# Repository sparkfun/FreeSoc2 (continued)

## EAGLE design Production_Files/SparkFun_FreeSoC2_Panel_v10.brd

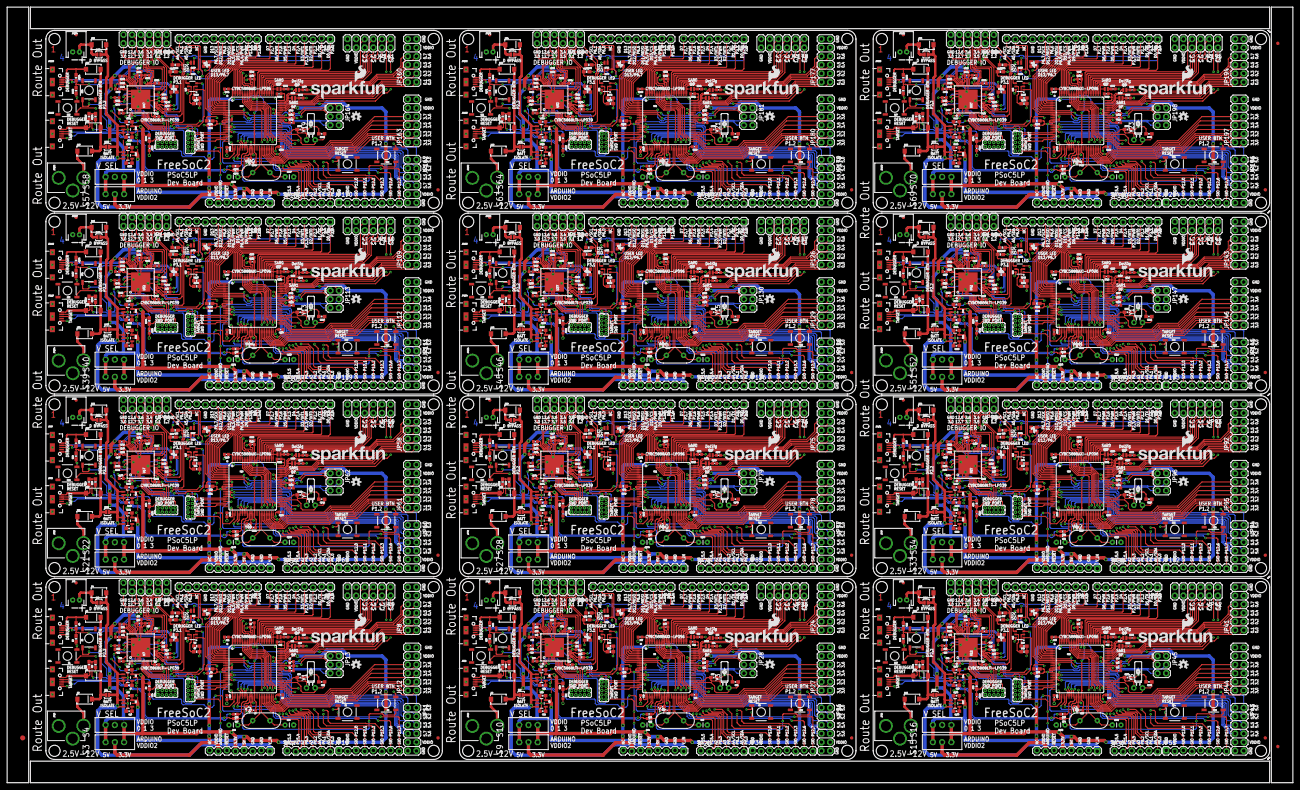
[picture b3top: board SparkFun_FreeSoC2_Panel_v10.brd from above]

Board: 4 copper layers, 379.0 x 228.6 mm, 1263 parts (0 on the bottom side), 1512 nets.

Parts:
C1, C2, C4, C5, C7, C16, C17, C19, C20, C39, C40, C41, C44, C45, C50, C51, C52, C53, C77, C78, C79, C82, C83, C88, C89, C90, C91, C115, C116, C117, C120, C121, C126, C127, C128, C129, C153, C154, C155, C158, C159, C164, C165, C166, C167, C191, C192, C193, C196, C197, C202, C203, C204, C205, C229, C230, C231, C234, C235, C240, C241, C242, C243, C267, C268, C269, C272, C273, C278, C279, C280, C281, C305, C306, C307, C310, C311, C316, C317, C318, C319, C343, C344, C345, C348, C349, C354, C355, C356, C357, C381, C382, C383, C386, C387, C392, C393, C394, C395, C419, C420, C421, C424, C425, C430, C431, C432, C433: 1.0uF; 0402-CAP
C3, C6, C9, C11, C13, C15, C21, C22, C23, C25, C27, C29, C30, C31, C32, C33, C34, C35, C36, C37, C38, C42, C43, C46, C47, C48, C49, C54, C55, C56, C57, C58, C59, C60, C69, C70, C71, C72, C73, C74, C75, C76, C80, C81, C84, C85, C86, C87, C92, C93, C94, C95, C96, C97, C98, C107, C108, C109, C110, C111, C112, C113, C114, C118, C119, C122, C123, C124, C125, C130, C131, C132, C133, C134, C135, C136, C145, C146, C147, C148, C149, C150, C151, C152, C156, C157, C160, C161, C162, C163, C168, C169, C170, C171, C172, C173, C174, C183, C184, C185, C186, C187, C188, C189, C190, C194, C195, C198, C199, C200, C201, C206, C207, C208, C209, C210, C211, C212, C221, C222, C223, C224, C225, C226, C227, C228, C232, C233, C236, C237, C238, C239, C244, C245, C246, C247, C248, C249, C250, C259, C260, C261, C262, C263, C264, C265, C266, C270, C271, C274, C275, C276, C277, C282, C283, C284, C285, C286, C287, C288, C297, C298, C299, C300, C301, C302, C303, C304, C308, C309, C312, C313, C314, C315, C320, C321, C322, C323, C324, C325, C326, C335, C336, C337, C338, C339, C340, C341, C342, C346, C347, C350, C351, C352, C353, C358, C359, C360, C361, C362, C363, C364, C373, C374, C375, C376, C377, C378, C379, C380, C384, C385, C388, C389, C390, C391, C396, C397, C398, C399, C400, C401, C402, C411, C412, C413, C414, C415, C416, C417, C418, C422, C423, C426, C427, C428, C429, C434, C435, C436, C437, C438, C439, C440, C449, C450, C451, C452, C453, C454, C455, C456: 0.1uF; 0402-CAP
C8, C10, C61, C62, C99, C100, C137, C138, C175, C176, C213, C214, C251, C252, C289, C290, C327, C328, C365, C366, C403, C404, C441, C442: 470pF; 0603-CAP
C12, C14, C63, C64, C101, C102, C139, C140, C177, C178, C215, C216, C253, C254, C291, C292, C329, C330, C367, C368, C405, C406, C443, C444: CAP-PTH-SMALL
C18, C24, C65, C66, C103, C104, C141, C142, C179, C180, C217, C218, C255, C256, C293, C294, C331, C332, C369, C370, C407, C408, C445, C446: 22pF; 0603-CAP
C26, C28, C67, C68, C105, C106, C143, C144, C181, C182, C219, C220, C257, C258, C295, C296, C333, C334, C371, C372, C409, C410, C447, C448: 2.2uF; 0603-CAP
D1, D2, D3, D4, D7, D8, D9, D10, D13, D14, D15, D16, D19, D20, D21, D22, D25, D26, D27, D28, D31, D32, D33, D34, D37, D38, D39, D40, D43, D44, D45, D46, D49, D50, D51, D52, D55, D56, D57, D58, D61, D62, D63, D64, D67, D68, D69, D70: MBRA140; SMA-DIODE
D5, D6, D11, D12, D17, D18, D23, D24, D29, D30, D35, D36, D41, D42, D47, D48, D53, D54, D59, D60, D65, D66, D71, D72: RED; LED-0603
E$1: FIDUCIAL-1.5X3
E$4, E$5: FIDUCIAL-1X2
FID1, FID2, FID3, FID4, FID5, FID6, FID7, FID8, FID9, FID10, FID11, FID12, FID13, FID14, FID15, FID16, FID17, FID18, FID19, FID20, FID21, FID22, FID23, FID24: FIDUCIAL1X2; FIDUCIAL-1X2
JP1, JP2, JP32, JP33, JP49, JP50, JP66, JP67, JP83, JP84, JP100, JP101, JP117, JP118, JP134, JP135, JP151, JP152, JP168, JP169, JP185, JP186, JP202, JP203: MicroB; USB-B-MICRO-SMD_V03
JP3, JP16, JP35, JP52, JP69, JP86, JP103, JP120, JP137, JP154, JP171, JP188: M02JST-PTH-2; JST-2-PTH
JP4, JP20, JP37, JP54, JP71, JP88, JP105, JP122, JP139, JP156, JP173, JP190: 1X6 FEMALE PTH; 1X06-SIP_LOCK
JP5, JP6, JP21, JP22, JP38, JP39, JP55, JP56, JP72, JP73, JP89, JP90, JP106, JP107, JP123, JP124, JP140, JP141, JP157, JP158, JP174, JP175, JP191, JP192: 1X8 FEMALE PTH; 1X08_LOCK
JP7, JP23, JP40, JP57, JP74, JP91, JP108, JP125, JP142, JP159, JP176, JP193: 1X10 FEMALE PTH; 1X10_LOCK
JP8, JP9, JP11, JP12, JP15, JP24, JP25, JP26, JP27, JP30, JP41, JP42, JP43, JP44, JP47, JP58, JP59, JP60, JP61, JP64, JP75, JP76, JP77, JP78, JP81, JP92, JP93, JP94, JP95, JP98, JP109, JP110, JP111, JP112, JP115, JP126, JP127, JP128, JP129, JP132, JP143, JP144, JP145, JP146, JP149, JP160, JP161, JP162, JP163, JP166, JP177, JP178, JP179, JP180, JP183, JP194, JP195, JP196, JP197, JP200: 2X6 FEMALE; 2X6
JP10, JP34, JP51, JP68, JP85, JP102, JP119, JP136, JP153, JP170, JP187, JP204: 1x8 FEMALE PTH; 1X08_LOCK
JP13, JP28, JP45, JP62, JP79, JP96, JP113, JP130, JP147, JP164, JP181, JP198: 2X3
JP14, JP17, JP29, JP31, JP46, JP48, JP63, JP65, JP80, JP82, JP97, JP99, JP114, JP116, JP131, JP133, JP148, JP150, JP165, JP167, JP182, JP184, JP199, JP201: DNP; 2X5_PTH_SILK_.05
JP18, JP19, JP36, JP53, JP70, JP87, JP104, JP121, JP138, JP155, JP172, JP189: POWER_JACKPTH_LOCK; POWER_JACK_PTH_LOCK
LOGO1, LOGO3, LOGO5, LOGO7, LOGO9, LOGO11, LOGO13, LOGO15, LOGO17, LOGO19, LOGO21, LOGO23: SFE_LOGO_NAME_FLAME.2_INCH; SFE_LOGO_NAME_FLAME_.2
LOGO2, LOGO4, LOGO6, LOGO8, LOGO10, LOGO12, LOGO14, LOGO16, LOGO18, LOGO20, LOGO22, LOGO24: OSHW-LOGOS; OSHW-LOGO-S
R1, R2, R23, R24, R39, R40, R55, R56, R71, R72, R87, R88, R103, R104, R119, R120, R135, R136, R151, R152, R167, R168, R183, R184: 4.7K; 0603-RES
R3, R4, R25, R26, R41, R42, R57, R58, R73, R74, R89, R90, R105, R106, R121, R122, R137, R138, R153, R154, R169, R170, R185, R186: 10K; 0603-RES
R5, R6, R27, R28, R43, R44, R59, R60, R75, R76, R91, R92, R107, R108, R123, R124, R139, R140, R155, R156, R171, R172, R187, R188: 20k; 0603-RES
R7, R8, R29, R30, R45, R46, R61, R62, R77, R78, R93, R94, R109, R110, R125, R126, R141, R142, R157, R158, R173, R174, R189, R190: 2.2k; 0603-RES
R9, R10, R15, R20, R21, R22, R31, R32, R37, R38, R47, R48, R53, R54, R63, R64, R69, R70, R79, R80, R85, R86, R95, R96, R101, R102, R111, R112, R117, R118, R127, R128, R133, R134, R143, R144, R149, R150, R159, R160, R165, R166, R175, R176, R181, R182, R191, R192: 1K; 0603-RES
R11, R12, R13, R14, R16, R17, R18, R19, R33, R34, R35, R36, R49, R50, R51, R52, R65, R66, R67, R68, R81, R82, R83, R84, R97, R98, R99, R100, R113, R114, R115, R116, R129, R130, R131, R132, R145, R146, R147, R148, R161, R162, R163, R164, R177, R178, R179, R180: 22; 0402-RES
S1, S2, S5, S6, S7, S8, S11, S12, S13, S14, S17, S18, S19, S20, S23, S24, S25, S26, S29, S30, S31, S32, S35, S36, S37, S38, S41, S42, S43, S44, S47, S48, S49, S50, S53, S54, S55, S56, S59, S60, S61, S62, S65, S66, S67, S68, S71, S72: SPST-MOM; TACTILE-SWITCH-SMD
S3, S4, S9, S10, S15, S16, S21, S22, S27, S28, S33, S34, S39, S40, S45, S46, S51, S52, S57, S58, S63, S64, S69, S70: SPDT; SWITCH-SPDT_LOCK.007S
SJ1, SJ8, SJ15, SJ22, SJ29, SJ36, SJ43, SJ50, SJ57, SJ64, SJ71, SJ78: JUMPER-PAD-2-NC_BY_PASTE; PAD-JUMPER-2-NC_BY_PASTE_YES_SILK
SJ2, SJ9, SJ16, SJ23, SJ30, SJ37, SJ44, SJ51, SJ58, SJ65, SJ72, SJ79: JUMPER-PAD-2-NOYES_SILK; PAD-JUMPER-2-NO_YES_SILK
SJ3, SJ4, SJ5, SJ6, SJ7, SJ10, SJ11, SJ12, SJ13, SJ14, SJ17, SJ18, SJ19, SJ20, SJ21, SJ24, SJ25, SJ26, SJ27, SJ28, SJ31, SJ32, SJ33, SJ34, SJ35, SJ38, SJ39, SJ40, SJ41, SJ42, SJ45, SJ46, SJ47, SJ48, SJ49, SJ52, SJ53, SJ54, SJ55, SJ56, SJ59, SJ60, SJ61, SJ62, SJ63, SJ66, SJ67, SJ68, SJ69, SJ70, SJ73, SJ74, SJ75, SJ76, SJ77, SJ80, SJ81, SJ82, SJ83, SJ84: JUMPER-PAD-2-NO; PAD-JUMPER-2-NO_NO_SILK
STANDOFF1, STANDOFF2, STANDOFF3, STANDOFF4, STANDOFF5, STANDOFF6, STANDOFF7, STANDOFF8, STANDOFF9, STANDOFF10, STANDOFF11, STANDOFF12, STANDOFF13, STANDOFF14, STANDOFF15, STANDOFF16, STANDOFF17, STANDOFF18, STANDOFF19, STANDOFF20, STANDOFF21, STANDOFF22, STANDOFF23, STANDOFF24, STANDOFF25, STANDOFF26, STANDOFF27, STANDOFF28, STANDOFF29, STANDOFF30, STANDOFF31, STANDOFF32, STANDOFF33, STANDOFF34, STANDOFF35, STANDOFF36, STANDOFF37, STANDOFF38, STANDOFF39, STANDOFF40, STANDOFF41, STANDOFF42, STANDOFF43, STANDOFF44, STANDOFF45, STANDOFF46, STANDOFF47, STANDOFF48: STAND-OFF
U1, U5, U11, U16, U21, U26, U31, U36, U41, U46, U51, U56: CY8C5888AXI-LP096; TQFP-100-14X14MM
U2, U8, U13, U18, U23, U28, U33, U38, U43, U48, U53, U58: MIC5219 5V; SOT23-5
U3, U9, U14, U19, U24, U29, U34, U39, U44, U49, U54, U59: MIC5219 3.3V; SOT23-5
U4, U10, U15, U20, U25, U30, U35, U40, U45, U50, U55, U60: 2A/20V; SOT26
U6, U7, U12, U17, U22, U27, U32, U37, U42, U47, U52, U57: CY8C5868LTI-LP039; QFN-68
Y1, Y3, Y5, Y7, Y9, Y11, Y13, Y15, Y17, Y19, Y21, Y23: 32.768kHz; TC26H
Y2, Y4, Y6, Y8, Y10, Y12, Y14, Y16, Y18, Y20, Y22, Y24: HC49US

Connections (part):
3.3V: C2.1, C3.1, C4.1, C19.1, C21.1, C22.1, C26.2, JP6.5, R1.2, R2.2, S3.3, S4.3, U1.37, U1.88, U3.5, U7.24, U7.59
3.3V1: C40.1, C43.1, C44.1, C52.1, C54.1, C55.1, C67.2, JP22.5, R23.2, R24.2, S9.3, S10.3, U5.37, U5.88, U6.24, U6.59, U9.5
3.3V2: C78.1, C81.1, C82.1, C90.1, C92.1, C93.1, C105.2, JP39.5, R39.2, R40.2, S15.3, S16.3, U11.37, U11.88, U12.24, U12.59, U14.5
3.3V3: C116.1, C119.1, C120.1, C128.1, C130.1, C131.1, C143.2, JP56.5, R55.2, R56.2, S21.3, S22.3, U16.37, U16.88, U17.24, U17.59, U19.5
3.3V4: C154.1, C157.1, C158.1, C166.1, C168.1, C169.1, C181.2, JP73.5, R71.2, R72.2, S27.3, S28.3, U21.37, U21.88, U22.24, U22.59, U24.5
3.3V5: C192.1, C195.1, C196.1, C204.1, C206.1, C207.1, C219.2, JP90.5, R87.2, R88.2, S33.3, S34.3, U26.37, U26.88, U27.24, U27.59, U29.5
3.3V6: C230.1, C233.1, C234.1, C242.1, C244.1, C245.1, C257.2, JP107.5, R103.2, R104.2, S39.3, S40.3, U31.37, U31.88, U32.24, U32.59, U34.5
3.3V7: C268.1, C271.1, C272.1, C280.1, C282.1, C283.1, C295.2, JP124.5, R119.2, R120.2, S45.3, S46.3, U36.37, U36.88, U37.24, U37.59, U39.5
3.3V8: C306.1, C309.1, C310.1, C318.1, C320.1, C321.1, C333.2, JP141.5, R135.2, R136.2, S51.3, S52.3, U41.37, U41.88, U42.24, U42.59, U44.5
3.3V9: C344.1, C347.1, C348.1, C356.1, C358.1, C359.1, C371.2, JP158.5, R151.2, R152.2, S57.3, S58.3, U46.37, U46.88, U47.24, U47.59, U49.5
3.3V10: C382.1, C385.1, C386.1, C394.1, C396.1, C397.1, C409.2, JP175.5, R167.2, R168.2, S63.3, S64.3, U51.37, U51.88, U52.24, U52.59, U54.5
3.3V11: C420.1, C423.1, C424.1, C432.1, C434.1, C435.1, C447.2, JP192.5, R183.2, R184.2, S69.3, S70.3, U56.37, U56.88, U57.24, U57.59, U59.5
5V: C5.1, C6.1, C20.1, C23.1, C28.2, JP6.4, S3.1, S4.1, U1.65, U2.5, U7.44
5V1: C41.1, C42.1, C53.1, C56.1, C68.2, JP22.4, S9.1, S10.1, U5.65, U6.44, U8.5
5V2: C79.1, C80.1, C91.1, C94.1, C106.2, JP39.4, S15.1, S16.1, U11.65, U12.44, U13.5
5V3: C117.1, C118.1, C129.1, C132.1, C144.2, JP56.4, S21.1, S22.1, U16.65, U17.44, U18.5
5V4: C155.1, C156.1, C167.1, C170.1, C182.2, JP73.4, S27.1, S28.1, U21.65, U22.44, U23.5
5V5: C193.1, C194.1, C205.1, C208.1, C220.2, JP90.4, S33.1, S34.1, U26.65, U27.44, U28.5
5V6: C231.1, C232.1, C243.1, C246.1, C258.2, JP107.4, S39.1, S40.1, U31.65, U32.44, U33.5
5V7: C269.1, C270.1, C281.1, C284.1, C296.2, JP124.4, S45.1, S46.1, U36.65, U37.44, U38.5
5V8: C307.1, C308.1, C319.1, C322.1, C334.2, JP141.4, S51.1, S52.1, U41.65, U42.44, U43.5
5V9: C345.1, C346.1, C357.1, C360.1, C372.2, JP158.4, S57.1, S58.1, U46.65, U47.44, U48.5
5V10: C383.1, C384.1, C395.1, C398.1, C410.2, JP175.4, S63.1, S64.1, U51.65, U52.44, U53.5
5V11: C421.1, C422.1, C433.1, C436.1, C448.2, JP192.4, S69.1, S70.1, U56.65, U57.44, U58.5
!DEBUG_P2.6_SCL_PU_EN: U4.G2, U7.1
!DEBUG_P2.6_SCL_PU_EN1: U6.1, U10.G2
!DEBUG_P2.6_SCL_PU_EN2: U12.1, U15.G2
!DEBUG_P2.6_SCL_PU_EN3: U17.1, U20.G2
!DEBUG_P2.6_SCL_PU_EN4: U22.1, U25.G2
!DEBUG_P2.6_SCL_PU_EN5: U27.1, U30.G2
!DEBUG_P2.6_SCL_PU_EN6: U32.1, U35.G2
!DEBUG_P2.6_SCL_PU_EN7: U37.1, U40.G2
!DEBUG_P2.6_SCL_PU_EN8: U42.1, U45.G2
!DEBUG_P2.6_SCL_PU_EN9: U47.1, U50.G2
!DEBUG_P2.6_SCL_PU_EN10: U52.1, U55.G2
!DEBUG_P2.6_SCL_PU_EN11: U57.1, U60.G2
!DEBUG_P2.7_SDA_PU_EN: U4.G1, U7.2
!DEBUG_P2.7_SDA_PU_EN1: U6.2, U10.G1
!DEBUG_P2.7_SDA_PU_EN2: U12.2, U15.G1
!DEBUG_P2.7_SDA_PU_EN3: U17.2, U20.G1
!DEBUG_P2.7_SDA_PU_EN4: U22.2, U25.G1
!DEBUG_P2.7_SDA_PU_EN5: U27.2, U30.G1
!DEBUG_P2.7_SDA_PU_EN6: U32.2, U35.G1
!DEBUG_P2.7_SDA_PU_EN7: U37.2, U40.G1
!DEBUG_P2.7_SDA_PU_EN8: U42.2, U45.G1
!DEBUG_P2.7_SDA_PU_EN9: U47.2, U50.G1
!DEBUG_P2.7_SDA_PU_EN10: U52.2, U55.G1
!DEBUG_P2.7_SDA_PU_EN11: U57.2, U60.G1
!DEBUG_RESET: C38.1, JP14.10, R2.1, S1.1, U7.10
!DEBUG_RESET1: C76.1, JP29.10, R24.1, S7.1, U6.10
!DEBUG_RESET2: C114.1, JP46.10, R40.1, S13.1, U12.10
!DEBUG_RESET3: C152.1, JP63.10, R56.1, S19.1, U17.10
!DEBUG_RESET4: C190.1, JP80.10, R72.1, S25.1, U22.10
!DEBUG_RESET5: C228.1, JP97.10, R88.1, S31.1, U27.10
!DEBUG_RESET6: C266.1, JP114.10, R104.1, S37.1, U32.10
!DEBUG_RESET7: C304.1, JP131.10, R120.1, S43.1, U37.10
!DEBUG_RESET8: C342.1, JP148.10, R136.1, S49.1, U42.10
!DEBUG_RESET9: C380.1, JP165.10, R152.1, S55.1, U47.10
!DEBUG_RESET10: C418.1, JP182.10, R168.1, S61.1, U52.10
!DEBUG_RESET11: C456.1, JP199.10, R184.1, S67.1, U57.10
!RESET: C37.1, JP6.6, JP13.5, JP17.10, R1.1, S2.1, U1.15, U7.3
!RESET1: C75.1, JP22.6, JP28.5, JP31.10, R23.1, S8.1, U5.15, U6.3
!RESET2: C113.1, JP39.6, JP45.5, JP48.10, R39.1, S14.1, U11.15, U12.3
!RESET3: C151.1, JP56.6, JP62.5, JP65.10, R55.1, S20.1, U16.15, U17.3
!RESET4: C189.1, JP73.6, JP79.5, JP82.10, R71.1, S26.1, U21.15, U22.3
!RESET5: C227.1, JP90.6, JP96.5, JP99.10, R87.1, S32.1, U26.15, U27.3
!RESET6: C265.1, JP107.6, JP113.5, JP116.10, R103.1, S38.1, U31.15, U32.3
!RESET7: C303.1, JP124.6, JP130.5, JP133.10, R119.1, S44.1, U36.15, U37.3
!RESET8: C341.1, JP141.6, JP147.5, JP150.10, R135.1, S50.1, U41.15, U42.3
!RESET9: C379.1, JP158.6, JP164.5, JP167.10, R151.1, S56.1, U46.15, U47.3
!RESET10: C417.1, JP175.6, JP181.5, JP184.10, R167.1, S62.1, U51.15, U52.3
!RESET11: C455.1, JP192.6, JP198.5, JP201.10, R183.1, S68.1, U56.15, U57.3
A0: JP4.1, U1.94
A1: JP4.2, U1.93
A2: JP4.3, U1.92
A3: JP4.4, U1.91
A4: JP4.5, JP7.10, SJ7.1, U1.90
A5: JP4.6, JP7.9, SJ6.1, U1.89
A6: JP20.1, U5.94
A7: JP20.2, U5.93
A8: JP20.6, JP23.9, SJ13.1, U5.89
A9: JP20.5, JP23.10, SJ14.1, U5.90
A10: JP20.3, U5.92
A11: JP20.4, U5.91
A12: JP37.1, U11.94
A13: JP37.2, U11.93
A14: JP37.6, JP40.9, SJ20.1, U11.89
A15: JP37.5, JP40.10, SJ21.1, U11.90
A16: JP37.3, U11.92
A17: JP37.4, U11.91
A18: JP54.1, U16.94
A19: JP54.2, U16.93
A20: JP54.6, JP57.9, SJ27.1, U16.89
A21: JP54.5, JP57.10, SJ28.1, U16.90
A22: JP54.3, U16.92
A23: JP54.4, U16.91
A24: JP71.1, U21.94
A25: JP71.2, U21.93
A26: JP71.6, JP74.9, SJ34.1, U21.89
A27: JP71.5, JP74.10, SJ35.1, U21.90
A28: JP71.3, U21.92
A29: JP71.4, U21.91
A30: JP88.1, U26.94
A31: JP88.2, U26.93
A32: JP88.6, JP91.9, SJ41.1, U26.89
A33: JP88.5, JP91.10, SJ42.1, U26.90
A34: JP88.3, U26.92
A35: JP88.4, U26.91
A36: JP105.1, U31.94
A37: JP105.2, U31.93
A38: JP105.6, JP108.9, SJ48.1, U31.89
A39: JP105.5, JP108.10, SJ49.1, U31.90
A40: JP105.3, U31.92
A41: JP105.4, U31.91
A42: JP122.1, U36.94
A43: JP122.2, U36.93
A44: JP122.6, JP125.9, SJ55.1, U36.89
A45: JP122.5, JP125.10, SJ56.1, U36.90
A46: JP122.3, U36.92
A47: JP122.4, U36.91
A48: JP139.1, U41.94
A49: JP139.2, U41.93
A50: JP139.6, JP142.9, SJ62.1, U41.89
A51: JP139.5, JP142.10, SJ63.1, U41.90
A52: JP139.3, U41.92
A53: JP139.4, U41.91
A54: JP156.1, U46.94
A55: JP156.2, U46.93
A56: JP156.6, JP159.9, SJ69.1, U46.89
A57: JP156.5, JP159.10, SJ70.1, U46.90
A58: JP156.3, U46.92
A59: JP156.4, U46.91
A60: JP173.1, U51.94
A61: JP173.2, U51.93
A62: JP173.6, JP176.9, SJ76.1, U51.89
A63: JP173.5, JP176.10, SJ77.1, U51.90
A64: JP173.3, U51.92
A65: JP173.4, U51.91
A66: JP190.1, U56.94
A67: JP190.2, U56.93
A68: JP190.6, JP193.9, SJ83.1, U56.89
A69: JP190.5, JP193.10, SJ84.1, U56.90
A70: JP190.3, U56.92
A71: JP190.4, U56.91
D0: JP5.1, R10.2, U1.95
D1: JP5.2, R9.2, U1.96
D2: JP5.3, U1.97
D3: JP5.4, U1.98
D4: JP5.5, U1.99
D5: JP5.6, U1.1
D6: JP5.7, U1.2
D7: JP5.8, U1.3
D8: JP7.1, U1.4
D9: JP7.2, U1.5
D10: JP7.3, U1.6
D11: JP7.4, JP13.4, U1.7
D12: JP7.5, JP13.1, U1.8
D13: JP7.6, JP13.3, R21.1, U1.9
D14: JP21.1, R32.2, U5.95
D15: JP21.2, R31.2, U5.96
D16: JP21.3, U5.97
D17: JP21.4, U5.98
D18: JP21.5, U5.99
D19: JP21.6, U5.1
D20: JP21.7, U5.2
D21: JP21.8, U5.3
D22: JP23.1, U5.4
D23: JP23.2, U5.5
D24: JP23.3, U5.6
D25: JP23.4, JP28.4, U5.7
D26: JP23.5, JP28.1, U5.8
D27: JP23.6, JP28.3, R22.1, U5.9
D28: JP38.1, R48.2, U11.95
D29: JP38.2, R47.2, U11.96
D30: JP38.3, U11.97
D31: JP38.4, U11.98
D32: JP38.5, U11.99
D33: JP38.6, U11.1
D34: JP38.7, U11.2
D35: JP38.8, U11.3
D36: JP40.1, U11.4
D37: JP40.2, U11.5
D38: JP40.3, U11.6
D39: JP40.4, JP45.4, U11.7
D40: JP40.5, JP45.1, U11.8
D41: JP40.6, JP45.3, R38.1, U11.9
D42: JP55.1, R64.2, U16.95
D43: JP55.2, R63.2, U16.96
D44: JP55.3, U16.97
D45: JP55.4, U16.98
D46: JP55.5, U16.99
D47: JP55.6, U16.1
D48: JP55.7, U16.2
D49: JP55.8, U16.3
D50: JP57.1, U16.4
D51: JP57.2, U16.5
D52: JP57.3, U16.6
D53: JP57.4, JP62.4, U16.7
D54: JP57.5, JP62.1, U16.8
D55: JP57.6, JP62.3, R54.1, U16.9
D56: JP72.1, R80.2, U21.95
D57: JP72.2, R79.2, U21.96
D58: JP72.3, U21.97
D59: JP72.4, U21.98
D60: JP72.5, U21.99
D61: JP72.6, U21.1
D62: JP72.7, U21.2
D63: JP72.8, U21.3
D64: JP74.1, U21.4
D65: JP74.2, U21.5
D66: JP74.3, U21.6
D67: JP74.4, JP79.4, U21.7
D68: JP74.5, JP79.1, U21.8
D69: JP74.6, JP79.3, R70.1, U21.9
D70: JP89.1, R96.2, U26.95
D71: JP89.2, R95.2, U26.96
D72: JP89.3, U26.97
D73: JP89.4, U26.98
D74: JP89.5, U26.99
D75: JP89.6, U26.1
D76: JP89.7, U26.2
D77: JP89.8, U26.3
D78: JP91.1, U26.4
D79: JP91.2, U26.5
D80: JP91.3, U26.6
D81: JP91.4, JP96.4, U26.7
D82: JP91.5, JP96.1, U26.8
D83: JP91.6, JP96.3, R86.1, U26.9
D84: JP106.1, R112.2, U31.95
D85: JP106.2, R111.2, U31.96
D86: JP106.3, U31.97
D87: JP106.4, U31.98
D88: JP106.5, U31.99
D89: JP106.6, U31.1
D90: JP106.7, U31.2
D91: JP106.8, U31.3
D92: JP108.1, U31.4
D93: JP108.2, U31.5
D94: JP108.3, U31.6
D95: JP108.4, JP113.4, U31.7
D96: JP108.5, JP113.1, U31.8
D97: JP108.6, JP113.3, R102.1, U31.9
D98: JP123.1, R128.2, U36.95
D99: JP123.2, R127.2, U36.96
D100: JP123.3, U36.97
D101: JP123.4, U36.98
D102: JP123.5, U36.99
D103: JP123.6, U36.1
D104: JP123.7, U36.2
D105: JP123.8, U36.3
D106: JP125.1, U36.4
D107: JP125.2, U36.5
D108: JP125.3, U36.6
D109: JP125.4, JP130.4, U36.7
D110: JP125.5, JP130.1, U36.8
D111: JP125.6, JP130.3, R118.1, U36.9
D112: JP140.1, R144.2, U41.95
D113: JP140.2, R143.2, U41.96
D114: JP140.3, U41.97
D115: JP140.4, U41.98
D116: JP140.5, U41.99
D117: JP140.6, U41.1
D118: JP140.7, U41.2
D119: JP140.8, U41.3
D120: JP142.1, U41.4
D121: JP142.2, U41.5
D122: JP142.3, U41.6
D123: JP142.4, JP147.4, U41.7
D124: JP142.5, JP147.1, U41.8
D125: JP142.6, JP147.3, R134.1, U41.9
D126: JP157.1, R160.2, U46.95
D127: JP157.2, R159.2, U46.96
D128: JP157.3, U46.97
D129: JP157.4, U46.98
D130: JP157.5, U46.99
D131: JP157.6, U46.1
D132: JP157.7, U46.2
D133: JP157.8, U46.3
D134: JP159.1, U46.4
D135: JP159.2, U46.5
D136: JP159.3, U46.6
D137: JP159.4, JP164.4, U46.7
D138: JP159.5, JP164.1, U46.8
D139: JP159.6, JP164.3, R150.1, U46.9
D140: JP174.1, R176.2, U51.95
D141: JP174.2, R175.2, U51.96
D142: JP174.3, U51.97
D143: JP174.4, U51.98
D144: JP174.5, U51.99
D145: JP174.6, U51.1
D146: JP174.7, U51.2
D147: JP174.8, U51.3
D148: JP176.1, U51.4
D149: JP176.2, U51.5
D150: JP176.3, U51.6
D151: JP176.4, JP181.4, U51.7
D152: JP176.5, JP181.1, U51.8
D153: JP176.6, JP181.3, R166.1, U51.9
D154: JP191.1, R192.2, U56.95
D155: JP191.2, R191.2, U56.96
D156: JP191.3, U56.97
D157: JP191.4, U56.98
D158: JP191.5, U56.99
D159: JP191.6, U56.1
D160: JP191.7, U56.2
D161: JP191.8, U56.3
D162: JP193.1, U56.4
D163: JP193.2, U56.5
D164: JP193.3, U56.6
D165: JP193.4, JP198.4, U56.7
D166: JP193.5, JP198.1, U56.8
D167: JP193.6, JP198.3, R182.1, U56.9
DEBUG_BTN: S5.1, U7.64
DEBUG_BTN1: S11.1, U6.64
DEBUG_BTN2: S17.1, U12.64
DEBUG_BTN3: S23.1, U17.64
DEBUG_BTN4: S29.1, U22.64
DEBUG_BTN5: S35.1, U27.64
DEBUG_BTN6: S41.1, U32.64
DEBUG_BTN7: S47.1, U37.64
DEBUG_BTN8: S53.1, U42.64
DEBUG_BTN9: S59.1, U47.64
DEBUG_BTN10: S65.1, U52.64
DEBUG_BTN11: S71.1, U57.64
DEBUG_D+_BUS: JP2.D+1, R18.2
DEBUG_D+_BUS1: JP33.D+1, R13.2
DEBUG_D+_BUS2: JP50.D+1, R35.2
DEBUG_D+_BUS3: JP67.D+1, R51.2
DEBUG_D+_BUS4: JP84.D+1, R67.2
DEBUG_D+_BUS5: JP101.D+1, R83.2
DEBUG_D+_BUS6: JP118.D+1, R99.2
DEBUG_D+_BUS7: JP135.D+1, R115.2
DEBUG_D+_BUS8: JP152.D+1, R131.2
DEBUG_D+_BUS9: JP169.D+1, R147.2
DEBUG_D+_BUS10: JP186.D+1, R163.2
DEBUG_D+_BUS11: JP203.D+1, R179.2
DEBUG_D+_PAD: R18.1, U7.22
DEBUG_D+_PAD1: R13.1, U6.22
DEBUG_D+_PAD2: R35.1, U12.22
DEBUG_D+_PAD3: R51.1, U17.22
DEBUG_D+_PAD4: R67.1, U22.22
DEBUG_D+_PAD5: R83.1, U27.22
DEBUG_D+_PAD6: R99.1, U32.22
DEBUG_D+_PAD7: R115.1, U37.22
DEBUG_D+_PAD8: R131.1, U42.22
DEBUG_D+_PAD9: R147.1, U47.22
DEBUG_D+_PAD10: R163.1, U52.22
DEBUG_D+_PAD11: R179.1, U57.22
DEBUG_D-_BUS: JP2.D-1, R19.2
DEBUG_D-_BUS1: JP33.D-1, R14.2
DEBUG_D-_BUS2: JP50.D-1, R36.2
DEBUG_D-_BUS3: JP67.D-1, R52.2
DEBUG_D-_BUS4: JP84.D-1, R68.2
DEBUG_D-_BUS5: JP101.D-1, R84.2
DEBUG_D-_BUS6: JP118.D-1, R100.2
DEBUG_D-_BUS7: JP135.D-1, R116.2
DEBUG_D-_BUS8: JP152.D-1, R132.2
DEBUG_D-_BUS9: JP169.D-1, R148.2
DEBUG_D-_BUS10: JP186.D-1, R164.2
DEBUG_D-_BUS11: JP203.D-1, R180.2
DEBUG_D-_PAD: R19.1, U7.23
DEBUG_D-_PAD1: R14.1, U6.23
DEBUG_D-_PAD2: R36.1, U12.23
DEBUG_D-_PAD3: R52.1, U17.23
DEBUG_D-_PAD4: R68.1, U22.23
DEBUG_D-_PAD5: R84.1, U27.23
DEBUG_D-_PAD6: R100.1, U32.23
DEBUG_D-_PAD7: R116.1, U37.23
DEBUG_D-_PAD8: R132.1, U42.23
DEBUG_D-_PAD9: R148.1, U47.23
DEBUG_D-_PAD10: R164.1, U52.23
DEBUG_D-_PAD11: R180.1, U57.23
DEBUG_DS_BP: C30.1, U7.51
DEBUG_DS_BP1: C69.1, U6.51
DEBUG_DS_BP2: C107.1, U12.51
DEBUG_DS_BP3: C145.1, U17.51
DEBUG_DS_BP4: C183.1, U22.51
DEBUG_DS_BP5: C221.1, U27.51
DEBUG_DS_BP6: C259.1, U32.51
DEBUG_DS_BP7: C297.1, U37.51
DEBUG_DS_BP8: C335.1, U42.51
DEBUG_DS_BP9: C373.1, U47.51
DEBUG_DS_BP10: C411.1, U52.51
DEBUG_DS_BP11: C449.1, U57.51
DEBUG_LED: R20.1, U7.30
DEBUG_LED1: R15.1, U6.30
DEBUG_LED2: R37.1, U12.30
DEBUG_LED3: R53.1, U17.30
DEBUG_LED4: R69.1, U22.30
DEBUG_LED5: R85.1, U27.30
DEBUG_LED6: R101.1, U32.30
DEBUG_LED7: R117.1, U37.30
DEBUG_LED8: R133.1, U42.30
DEBUG_LED9: R149.1, U47.30
DEBUG_LED10: R165.1, U52.30
DEBUG_LED11: R181.1, U57.30
DEBUG_P0.0: JP15.3, U7.48
DEBUG_P0.1: JP15.4, U7.49
DEBUG_P0.2: JP30.3, U6.48
DEBUG_P0.3: JP30.4, U6.49
DEBUG_P0.4: JP47.3, U12.48
DEBUG_P0.5: JP47.4, U12.49
DEBUG_P0.6: JP64.3, U17.48
DEBUG_P0.7: JP64.4, U17.49
DEBUG_P0.8: JP81.3, U22.48
DEBUG_P0.9: JP81.4, U22.49
DEBUG_P0.10: JP98.3, U27.48
DEBUG_P0.11: JP98.4, U27.49
DEBUG_P0.12: JP115.3, U32.48
DEBUG_P0.13: JP115.4, U32.49
DEBUG_P0.14: JP132.3, U37.48
DEBUG_P0.15: JP132.4, U37.49
DEBUG_P0.16: JP149.3, U42.48
DEBUG_P0.17: JP149.4, U42.49
DEBUG_P0.18: JP166.3, U47.48
DEBUG_P0.19: JP166.4, U47.49
DEBUG_P0.20: JP183.3, U52.48
DEBUG_P0.21: JP183.4, U52.49
DEBUG_P0.22: JP200.3, U57.48
DEBUG_P0.23: JP200.4, U57.49
DEBUG_P1.1: JP30.2, U6.13
DEBUG_P1.2: JP15.2, U7.13
DEBUG_P1.3: JP47.2, U12.13
DEBUG_P1.4: JP64.2, U17.13
DEBUG_P1.5: JP81.2, U22.13
DEBUG_P1.6: JP98.2, U27.13
DEBUG_P1.7: JP115.2, U32.13
DEBUG_P1.8: JP132.2, U37.13
DEBUG_P1.9: JP149.2, U42.13
DEBUG_P1.10: JP166.2, U47.13
DEBUG_P1.11: JP183.2, U52.13
DEBUG_P1.12: JP200.2, U57.13
DEBUG_P3.0: JP15.12, U7.29
DEBUG_P3.1: JP30.5, U6.33
DEBUG_P3.2: JP30.6, U6.34
DEBUG_P3.3: JP30.7, U6.36
DEBUG_P3.4: JP15.5, U7.33
DEBUG_P3.5: JP15.6, U7.34
DEBUG_P3.6: JP15.7, U7.36
DEBUG_P3.7: JP15.8, U7.37
DEBUG_P3.8: JP30.8, U6.37
DEBUG_P3.9: JP30.12, U6.29
DEBUG_P3.10: JP47.5, U12.33
DEBUG_P3.11: JP47.6, U12.34
DEBUG_P3.12: JP47.7, U12.36
DEBUG_P3.13: JP47.8, U12.37
DEBUG_P3.14: JP47.12, U12.29
DEBUG_P3.15: JP64.5, U17.33
DEBUG_P3.16: JP64.6, U17.34
DEBUG_P3.17: JP64.7, U17.36
DEBUG_P3.18: JP64.8, U17.37
DEBUG_P3.19: JP64.12, U17.29
DEBUG_P3.20: JP81.5, U22.33
DEBUG_P3.21: JP81.6, U22.34
DEBUG_P3.22: JP81.7, U22.36
DEBUG_P3.23: JP81.8, U22.37
DEBUG_P3.24: JP81.12, U22.29
DEBUG_P3.25: JP98.5, U27.33
DEBUG_P3.26: JP98.6, U27.34
DEBUG_P3.27: JP98.7, U27.36
DEBUG_P3.28: JP98.8, U27.37
DEBUG_P3.29: JP98.12, U27.29
DEBUG_P3.30: JP115.5, U32.33
DEBUG_P3.31: JP115.6, U32.34
DEBUG_P3.32: JP115.7, U32.36
DEBUG_P3.33: JP115.8, U32.37
DEBUG_P3.34: JP115.12, U32.29
DEBUG_P3.35: JP132.5, U37.33
DEBUG_P3.36: JP132.6, U37.34
DEBUG_P3.37: JP132.7, U37.36
DEBUG_P3.38: JP132.8, U37.37
DEBUG_P3.39: JP132.12, U37.29
DEBUG_P3.40: JP149.5, U42.33
DEBUG_P3.41: JP149.6, U42.34
DEBUG_P3.42: JP149.7, U42.36
DEBUG_P3.43: JP149.8, U42.37
DEBUG_P3.44: JP149.12, U42.29
DEBUG_P3.45: JP166.5, U47.33
DEBUG_P3.46: JP166.6, U47.34
DEBUG_P3.47: JP166.7, U47.36
DEBUG_P3.48: JP166.8, U47.37
DEBUG_P3.49: JP166.12, U47.29
DEBUG_P3.50: JP183.5, U52.33
DEBUG_P3.51: JP183.6, U52.34
DEBUG_P3.52: JP183.7, U52.36
DEBUG_P3.53: JP183.8, U52.37
DEBUG_P3.54: JP183.12, U52.29
DEBUG_P3.55: JP200.5, U57.33
DEBUG_P3.56: JP200.6, U57.34
DEBUG_P3.57: JP200.7, U57.36
DEBUG_P3.58: JP200.8, U57.37
DEBUG_P3.59: JP200.12, U57.29
DEBUG_P12.0_SCL: SJ7.2, U4.D2, U7.39
DEBUG_P12.0_SCL1: SJ14.2, U6.39, U10.D2
DEBUG_P12.0_SCL2: SJ21.2, U12.39, U15.D2
DEBUG_P12.0_SCL3: SJ28.2, U17.39, U20.D2
DEBUG_P12.0_SCL4: SJ35.2, U22.39, U25.D2
DEBUG_P12.0_SCL5: SJ42.2, U27.39, U30.D2
DEBUG_P12.0_SCL6: SJ49.2, U32.39, U35.D2
DEBUG_P12.0_SCL7: SJ56.2, U37.39, U40.D2
DEBUG_P12.0_SCL8: SJ63.2, U42.39, U45.D2
DEBUG_P12.0_SCL9: SJ70.2, U47.39, U50.D2
DEBUG_P12.0_SCL10: SJ77.2, U52.39, U55.D2
DEBUG_P12.0_SCL11: SJ84.2, U57.39, U60.D2
DEBUG_P12.1_SDA: SJ6.2, U4.D1, U7.38
DEBUG_P12.1_SDA1: SJ13.2, U6.38, U10.D1
DEBUG_P12.1_SDA2: SJ20.2, U12.38, U15.D1
DEBUG_P12.1_SDA3: SJ27.2, U17.38, U20.D1
DEBUG_P12.1_SDA4: SJ34.2, U22.38, U25.D1
DEBUG_P12.1_SDA5: SJ41.2, U27.38, U30.D1
DEBUG_P12.1_SDA6: SJ48.2, U32.38, U35.D1
DEBUG_P12.1_SDA7: SJ55.2, U37.38, U40.D1
DEBUG_P12.1_SDA8: SJ62.2, U42.38, U45.D1
DEBUG_P12.1_SDA9: SJ69.2, U47.38, U50.D1
DEBUG_P12.1_SDA10: SJ76.2, U52.38, U55.D1
DEBUG_P12.1_SDA11: SJ83.2, U57.38, U60.D1
DEBUG_P12.6_RX: JP15.9, R9.1, U7.20
DEBUG_P12.6_RX1: JP30.9, R31.1, U6.20
DEBUG_P12.6_RX2: JP47.9, R47.1, U12.20
DEBUG_P12.6_RX3: JP64.9, R63.1, U17.20
DEBUG_P12.6_RX4: JP81.9, R79.1, U22.20
DEBUG_P12.6_RX5: JP98.9, R95.1, U27.20
DEBUG_P12.6_RX6: JP115.9, R111.1, U32.20
DEBUG_P12.6_RX7: JP132.9, R127.1, U37.20
DEBUG_P12.6_RX8: JP149.9, R143.1, U42.20
DEBUG_P12.6_RX9: JP166.9, R159.1, U47.20
DEBUG_P12.6_RX10: JP183.9, R175.1, U52.20
DEBUG_P12.6_RX11: JP200.9, R191.1, U57.20
DEBUG_P12.7_TX: JP15.10, R10.1, U7.21
DEBUG_P12.7_TX1: JP30.10, R32.1, U6.21
DEBUG_P12.7_TX2: JP47.10, R48.1, U12.21
DEBUG_P12.7_TX3: JP64.10, R64.1, U17.21
DEBUG_P12.7_TX4: JP81.10, R80.1, U22.21
DEBUG_P12.7_TX5: JP98.10, R96.1, U27.21
DEBUG_P12.7_TX6: JP115.10, R112.1, U32.21
DEBUG_P12.7_TX7: JP132.10, R128.1, U37.21
DEBUG_P12.7_TX8: JP149.10, R144.1, U42.21
DEBUG_P12.7_TX9: JP166.10, R160.1, U47.21
DEBUG_P12.7_TX10: JP183.10, R176.1, U52.21
DEBUG_P12.7_TX11: JP200.10, R192.1, U57.21
DEBUG_SAR0_BP: C33.1, U7.53
DEBUG_SAR0_BP1: C71.1, U6.53
DEBUG_SAR0_BP2: C109.1, U12.53
DEBUG_SAR0_BP3: C147.1, U17.53
DEBUG_SAR0_BP4: C185.1, U22.53
DEBUG_SAR0_BP5: C223.1, U27.53
DEBUG_SAR0_BP6: C261.1, U32.53
DEBUG_SAR0_BP7: C299.1, U37.53
DEBUG_SAR0_BP8: C337.1, U42.53
DEBUG_SAR0_BP9: C375.1, U47.53
DEBUG_SAR0_BP10: C413.1, U52.53
DEBUG_SAR0_BP11: C451.1, U57.53
DEBUG_SAR1_BP: C32.1, U7.50
DEBUG_SAR1_BP1: C70.1, U6.50
DEBUG_SAR1_BP2: C108.1, U12.50
DEBUG_SAR1_BP3: C146.1, U17.50
DEBUG_SAR1_BP4: C184.1, U22.50
DEBUG_SAR1_BP5: C222.1, U27.50
DEBUG_SAR1_BP6: C260.1, U32.50
DEBUG_SAR1_BP7: C298.1, U37.50
DEBUG_SAR1_BP8: C336.1, U42.50
DEBUG_SAR1_BP9: C374.1, U47.50
DEBUG_SAR1_BP10: C412.1, U52.50
DEBUG_SAR1_BP11: C450.1, U57.50
DEBUG_SWDCK_TCK: JP14.4, U7.12
DEBUG_SWDCK_TCK1: JP29.4, U6.12
DEBUG_SWDCK_TCK2: JP46.4, U12.12
DEBUG_SWDCK_TCK3: JP63.4, U17.12
DEBUG_SWDCK_TCK4: JP80.4, U22.12
DEBUG_SWDCK_TCK5: JP97.4, U27.12
DEBUG_SWDCK_TCK6: JP114.4, U32.12
DEBUG_SWDCK_TCK7: JP131.4, U37.12
DEBUG_SWDCK_TCK8: JP148.4, U42.12
DEBUG_SWDCK_TCK9: JP165.4, U47.12
DEBUG_SWDCK_TCK10: JP182.4, U52.12
DEBUG_SWDCK_TCK11: JP199.4, U57.12
DEBUG_SWDIO_TMS: JP14.2, U7.11
DEBUG_SWDIO_TMS1: JP29.2, U6.11
DEBUG_SWDIO_TMS2: JP46.2, U12.11
DEBUG_SWDIO_TMS3: JP63.2, U17.11
DEBUG_SWDIO_TMS4: JP80.2, U22.11
DEBUG_SWDIO_TMS5: JP97.2, U27.11
DEBUG_SWDIO_TMS6: JP114.2, U32.11
DEBUG_SWDIO_TMS7: JP131.2, U37.11
DEBUG_SWDIO_TMS8: JP148.2, U42.11
DEBUG_SWDIO_TMS9: JP165.2, U47.11
DEBUG_SWDIO_TMS10: JP182.2, U52.11
DEBUG_SWDIO_TMS11: JP199.2, U57.11
DEBUG_SWV_TDO: JP14.6, U7.14
DEBUG_SWV_TDO1: JP29.6, U6.14
DEBUG_SWV_TDO2: JP46.6, U12.14
DEBUG_SWV_TDO3: JP63.6, U17.14
DEBUG_SWV_TDO4: JP80.6, U22.14
DEBUG_SWV_TDO5: JP97.6, U27.14
DEBUG_SWV_TDO6: JP114.6, U32.14
DEBUG_SWV_TDO7: JP131.6, U37.14
DEBUG_SWV_TDO8: JP148.6, U42.14
DEBUG_SWV_TDO9: JP165.6, U47.14
DEBUG_SWV_TDO10: JP182.6, U52.14
DEBUG_SWV_TDO11: JP199.6, U57.14
DEBUG_TDI: JP14.8, U7.15
DEBUG_TDI1: JP29.8, U6.15
DEBUG_TDI2: JP46.8, U12.15
DEBUG_TDI3: JP63.8, U17.15
DEBUG_TDI4: JP80.8, U22.15
DEBUG_TDI5: JP97.8, U27.15
DEBUG_TDI6: JP114.8, U32.15
DEBUG_TDI7: JP131.8, U37.15
DEBUG_TDI8: JP148.8, U42.15
DEBUG_TDI9: JP165.8, U47.15
DEBUG_TDI10: JP182.8, U52.15
DEBUG_TDI11: JP199.8, U57.15
GND: C1.2, C2.2, C3.2, C4.2, C5.2, C6.2, C7.2, C8.2, C9.2, C10.2, C11.2, C12.2, C13.2, C14.2, C15.2, C16.2, C17.2, C18.2, C19.2, C20.2, C21.2, C22.2, C23.2, C24.2, C25.2, C26.1, C27.2, C28.1, C29.2, C30.2, C31.2, C32.2, C33.2, C34.2, C35.2, C36.2, C37.2, C38.2, D5.C, D6.C, JP1.GND1, JP1.SHIELD1, JP1.SHIELD2, JP1.SHIELD3, JP2.GND1, JP2.SHIELD1, JP2.SHIELD2, JP2.SHIELD3, JP3.1, JP6.2, JP6.3, JP7.7, JP8.11, JP8.12, JP9.11, JP9.12, JP10.1, JP11.11, JP11.12, JP12.11, JP12.12, JP13.6, JP14.3, JP14.5, JP14.7, JP14.9, JP15.11, JP17.3, JP17.5, JP17.7, JP17.9, JP18.GND, JP18.GNDBREAK, R5.1, R6.1, S1.3, S2.3, S5.3, S6.3, U1.10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
GND1: C39.2, C40.2, C41.2, C42.2, C43.2, C44.2, C45.2, C46.2, C47.2, C48.2, C49.2, C50.2, C51.2, C52.2, C53.2, C54.2, C55.2, C56.2, C57.2, C58.2, C59.2, C60.2, C61.2, C62.2, C63.2, C64.2, C65.2, C66.2, C67.1, C68.1, C69.2, C70.2, C71.2, C72.2, C73.2, C74.2, C75.2, C76.2, D11.C, D12.C, JP16.1, JP19.GND, JP19.GNDBREAK, JP22.2, JP22.3, JP23.7, JP24.11, JP24.12, JP25.11, JP25.12, JP26.11, JP26.12, JP27.11, JP27.12, JP28.6, JP29.3, JP29.5, JP29.7, JP29.9, JP30.11, JP31.3, JP31.5, JP31.7, JP31.9, JP32.GND1, JP32.SHIELD1, JP32.SHIELD2, JP32.SHIELD3, JP33.GND1, JP33.SHIELD1, JP33.SHIELD2, JP33.SHIELD3, JP34.1, R27.1, R28.1, S7.3, S8.3, S11.3, S12.3, U5.10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
GND2: C77.2, C78.2, C79.2, C80.2, C81.2, C82.2, C83.2, C84.2, C85.2, C86.2, C87.2, C88.2, C89.2, C90.2, C91.2, C92.2, C93.2, C94.2, C95.2, C96.2, C97.2, C98.2, C99.2, C100.2, C101.2, C102.2, C103.2, C104.2, C105.1, C106.1, C107.2, C108.2, C109.2, C110.2, C111.2, C112.2, C113.2, C114.2, D17.C, D18.C, JP35.1, JP36.GND, JP36.GNDBREAK, JP39.2, JP39.3, JP40.7, JP41.11, JP41.12, JP42.11, JP42.12, JP43.11, JP43.12, JP44.11, JP44.12, JP45.6, JP46.3, JP46.5, JP46.7, JP46.9, JP47.11, JP48.3, JP48.5, JP48.7, JP48.9, JP49.GND1, JP49.SHIELD1, JP49.SHIELD2, JP49.SHIELD3, JP50.GND1, JP50.SHIELD1, JP50.SHIELD2, JP50.SHIELD3, JP51.1, R43.1, R44.1, S13.3, S14.3, S17.3, S18.3, U11.10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
GND3: C115.2, C116.2, C117.2, C118.2, C119.2, C120.2, C121.2, C122.2, C123.2, C124.2, C125.2, C126.2, C127.2, C128.2, C129.2, C130.2, C131.2, C132.2, C133.2, C134.2, C135.2, C136.2, C137.2, C138.2, C139.2, C140.2, C141.2, C142.2, C143.1, C144.1, C145.2, C146.2, C147.2, C148.2, C149.2, C150.2, C151.2, C152.2, D23.C, D24.C, JP52.1, JP53.GND, JP53.GNDBREAK, JP56.2, JP56.3, JP57.7, JP58.11, JP58.12, JP59.11, JP59.12, JP60.11, JP60.12, JP61.11, JP61.12, JP62.6, JP63.3, JP63.5, JP63.7, JP63.9, JP64.11, JP65.3, JP65.5, JP65.7, JP65.9, JP66.GND1, JP66.SHIELD1, JP66.SHIELD2, JP66.SHIELD3, JP67.GND1, JP67.SHIELD1, JP67.SHIELD2, JP67.SHIELD3, JP68.1, R59.1, R60.1, S19.3, S20.3, S23.3, S24.3, U16.10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
GND4: C153.2, C154.2, C155.2, C156.2, C157.2, C158.2, C159.2, C160.2, C161.2, C162.2, C163.2, C164.2, C165.2, C166.2, C167.2, C168.2, C169.2, C170.2, C171.2, C172.2, C173.2, C174.2, C175.2, C176.2, C177.2, C178.2, C179.2, C180.2, C181.1, C182.1, C183.2, C184.2, C185.2, C186.2, C187.2, C188.2, C189.2, C190.2, D29.C, D30.C, JP69.1, JP70.GND, JP70.GNDBREAK, JP73.2, JP73.3, JP74.7, JP75.11, JP75.12, JP76.11, JP76.12, JP77.11, JP77.12, JP78.11, JP78.12, JP79.6, JP80.3, JP80.5, JP80.7, JP80.9, JP81.11, JP82.3, JP82.5, JP82.7, JP82.9, JP83.GND1, JP83.SHIELD1, JP83.SHIELD2, JP83.SHIELD3, JP84.GND1, JP84.SHIELD1, JP84.SHIELD2, JP84.SHIELD3, JP85.1, R75.1, R76.1, S25.3, S26.3, S29.3, S30.3, U21.10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
GND5: C191.2, C192.2, C193.2, C194.2, C195.2, C196.2, C197.2, C198.2, C199.2, C200.2, C201.2, C202.2, C203.2, C204.2, C205.2, C206.2, C207.2, C208.2, C209.2, C210.2, C211.2, C212.2, C213.2, C214.2, C215.2, C216.2, C217.2, C218.2, C219.1, C220.1, C221.2, C222.2, C223.2, C224.2, C225.2, C226.2, C227.2, C228.2, D35.C, D36.C, JP86.1, JP87.GND, JP87.GNDBREAK, JP90.2, JP90.3, JP91.7, JP92.11, JP92.12, JP93.11, JP93.12, JP94.11, JP94.12, JP95.11, JP95.12, JP96.6, JP97.3, JP97.5, JP97.7, JP97.9, JP98.11, JP99.3, JP99.5, JP99.7, JP99.9, JP100.GND1, JP100.SHIELD1, JP100.SHIELD2, JP100.SHIELD3, JP101.GND1, JP101.SHIELD1, JP101.SHIELD2, JP101.SHIELD3, JP102.1, R91.1, R92.1, S31.3, S32.3, S35.3, S36.3, U26.10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
GND6: C229.2, C230.2, C231.2, C232.2, C233.2, C234.2, C235.2, C236.2, C237.2, C238.2, C239.2, C240.2, C241.2, C242.2, C243.2, C244.2, C245.2, C246.2, C247.2, C248.2, C249.2, C250.2, C251.2, C252.2, C253.2, C254.2, C255.2, C256.2, C257.1, C258.1, C259.2, C260.2, C261.2, C262.2, C263.2, C264.2, C265.2, C266.2, D41.C, D42.C, JP103.1, JP104.GND, JP104.GNDBREAK, JP107.2, JP107.3, JP108.7, JP109.11, JP109.12, JP110.11, JP110.12, JP111.11, JP111.12, JP112.11, JP112.12, JP113.6, JP114.3, JP114.5, JP114.7, JP114.9, JP115.11, JP116.3, JP116.5, JP116.7, JP116.9, JP117.GND1, JP117.SHIELD1, JP117.SHIELD2, JP117.SHIELD3, JP118.GND1, JP118.SHIELD1, JP118.SHIELD2, JP118.SHIELD3, JP119.1, R107.1, R108.1, S37.3, S38.3, S41.3, S42.3, U31.10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
GND7: C267.2, C268.2, C269.2, C270.2, C271.2, C272.2, C273.2, C274.2, C275.2, C276.2, C277.2, C278.2, C279.2, C280.2, C281.2, C282.2, C283.2, C284.2, C285.2, C286.2, C287.2, C288.2, C289.2, C290.2, C291.2, C292.2, C293.2, C294.2, C295.1, C296.1, C297.2, C298.2, C299.2, C300.2, C301.2, C302.2, C303.2, C304.2, D47.C, D48.C, JP120.1, JP121.GND, JP121.GNDBREAK, JP124.2, JP124.3, JP125.7, JP126.11, JP126.12, JP127.11, JP127.12, JP128.11, JP128.12, JP129.11, JP129.12, JP130.6, JP131.3, JP131.5, JP131.7, JP131.9, JP132.11, JP133.3, JP133.5, JP133.7, JP133.9, JP134.GND1, JP134.SHIELD1, JP134.SHIELD2, JP134.SHIELD3, JP135.GND1, JP135.SHIELD1, JP135.SHIELD2, JP135.SHIELD3, JP136.1, R123.1, R124.1, S43.3, S44.3, S47.3, S48.3, U36.10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
GND8: C305.2, C306.2, C307.2, C308.2, C309.2, C310.2, C311.2, C312.2, C313.2, C314.2, C315.2, C316.2, C317.2, C318.2, C319.2, C320.2, C321.2, C322.2, C323.2, C324.2, C325.2, C326.2, C327.2, C328.2, C329.2, C330.2, C331.2, C332.2, C333.1, C334.1, C335.2, C336.2, C337.2, C338.2, C339.2, C340.2, C341.2, C342.2, D53.C, D54.C, JP137.1, JP138.GND, JP138.GNDBREAK, JP141.2, JP141.3, JP142.7, JP143.11, JP143.12, JP144.11, JP144.12, JP145.11, JP145.12, JP146.11, JP146.12, JP147.6, JP148.3, JP148.5, JP148.7, JP148.9, JP149.11, JP150.3, JP150.5, JP150.7, JP150.9, JP151.GND1, JP151.SHIELD1, JP151.SHIELD2, JP151.SHIELD3, JP152.GND1, JP152.SHIELD1, JP152.SHIELD2, JP152.SHIELD3, JP153.1, R139.1, R140.1, S49.3, S50.3, S53.3, S54.3, U41.10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
GND9: C343.2, C344.2, C345.2, C346.2, C347.2, C348.2, C349.2, C350.2, C351.2, C352.2, C353.2, C354.2, C355.2, C356.2, C357.2, C358.2, C359.2, C360.2, C361.2, C362.2, C363.2, C364.2, C365.2, C366.2, C367.2, C368.2, C369.2, C370.2, C371.1, C372.1, C373.2, C374.2, C375.2, C376.2, C377.2, C378.2, C379.2, C380.2, D59.C, D60.C, JP154.1, JP155.GND, JP155.GNDBREAK, JP158.2, JP158.3, JP159.7, JP160.11, JP160.12, JP161.11, JP161.12, JP162.11, JP162.12, JP163.11, JP163.12, JP164.6, JP165.3, JP165.5, JP165.7, JP165.9, JP166.11, JP167.3, JP167.5, JP167.7, JP167.9, JP168.GND1, JP168.SHIELD1, JP168.SHIELD2, JP168.SHIELD3, JP169.GND1, JP169.SHIELD1, JP169.SHIELD2, JP169.SHIELD3, JP170.1, R155.1, R156.1, S55.3, S56.3, S59.3, S60.3, U46.10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
GND10: C381.2, C382.2, C383.2, C384.2, C385.2, C386.2, C387.2, C388.2, C389.2, C390.2, C391.2, C392.2, C393.2, C394.2, C395.2, C396.2, C397.2, C398.2, C399.2, C400.2, C401.2, C402.2, C403.2, C404.2, C405.2, C406.2, C407.2, C408.2, C409.1, C410.1, C411.2, C412.2, C413.2, C414.2, C415.2, C416.2, C417.2, C418.2, D65.C, D66.C, JP171.1, JP172.GND, JP172.GNDBREAK, JP175.2, JP175.3, JP176.7, JP177.11, JP177.12, JP178.11, JP178.12, JP179.11, JP179.12, JP180.11, JP180.12, JP181.6, JP182.3, JP182.5, JP182.7, JP182.9, JP183.11, JP184.3, JP184.5, JP184.7, JP184.9, JP185.GND1, JP185.SHIELD1, JP185.SHIELD2, JP185.SHIELD3, JP186.GND1, JP186.SHIELD1, JP186.SHIELD2, JP186.SHIELD3, JP187.1, R171.1, R172.1, S61.3, S62.3, S65.3, S66.3, U51.10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
GND11: C419.2, C420.2, C421.2, C422.2, C423.2, C424.2, C425.2, C426.2, C427.2, C428.2, C429.2, C430.2, C431.2, C432.2, C433.2, C434.2, C435.2, C436.2, C437.2, C438.2, C439.2, C440.2, C441.2, C442.2, C443.2, C444.2, C445.2, C446.2, C447.1, C448.1, C449.2, C450.2, C451.2, C452.2, C453.2, C454.2, C455.2, C456.2, D71.C, D72.C, JP188.1, JP189.GND, JP189.GNDBREAK, JP192.2, JP192.3, JP193.7, JP194.11, JP194.12, JP195.11, JP195.12, JP196.11, JP196.12, JP197.11, JP197.12, JP198.6, JP199.3, JP199.5, JP199.7, JP199.9, JP200.11, JP201.3, JP201.5, JP201.7, JP201.9, JP202.GND1, JP202.SHIELD1, JP202.SHIELD2, JP202.SHIELD3, JP203.GND1, JP203.SHIELD1, JP203.SHIELD2, JP203.SHIELD3, JP204.1, R187.1, R188.1, S67.3, S68.3, S71.3, S72.3, U56.10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
unnamed: C8.1, U3.4
unnamed: C10.1, U2.4
unnamed: C34.1, SJ5.2
unnamed: C35.1, SJ4.2
unnamed: C36.1, SJ3.2
unnamed: D9.A, JP19.PWR
unnamed: R8.1, U4.S2
unnamed: R7.1, U4.S1
unnamed: D7.C, D8.C, D9.C, SJ8.1
unnamed: D10.A, JP16.2, SJ9.1
unnamed: C50.1, U6.26, U6.57
unnamed: D12.A, R15.2
unnamed: D3.A, JP18.PWR
unnamed: C16.1, U7.26, U7.57
unnamed: D11.A, R22.2
unnamed: D1.C, D2.C, D3.C, SJ1.1
unnamed: D4.A, JP3.2, SJ2.1
unnamed: C51.1, U6.42
unnamed: C61.1, U9.4
unnamed: C62.1, U8.4
unnamed: C72.1, SJ12.2
unnamed: C73.1, SJ11.2
unnamed: D6.A, R20.2
unnamed: C74.1, SJ10.2
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
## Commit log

2014-10-21 Commit first schematic
2014-10-22 Add some bypass caps
2014-10-30 Routed, ready for review.
2014-11-10 Routed, with board checklist.
2014-11-11 Ready for QC review
2014-11-14 Fixed stuff from QC spreadsheet review.
2014-11-17 Files as submitted to Advanced, with prototype Gerbers
2015-01-12 Files changed after v01 feedback, to add kitprog ID pins
2015-01-19 Changes for v02 in, review
2015-01-19 ready for protos v02
2015-01-20 Up to V02, checklist and peer review completed
2015-02-10 v10 almost ready
2015-02-11 Changes for v10, pre-review
2015-02-11 Renamed files, added FreeSoC2 name
2015-02-12 Add UART/I2C bridge, lock headers, IC names
2015-02-13 Fixed a few small errors from staggered headers.
2015-02-13 Revisions from QC check
2015-02-13 Fixed silk/part value for target IC
2015-02-13 Add prod_id info to some parts
2015-02-25 created massive panel v10
2015-03-20 Rev to 11 to fix rev #, layers issue
2015-03-20 deleted old panel with missing ground
2015-03-20 created panel v11
    includes gerbers for verification
2015-04-10 Rev to include changes from production
2015-05-19 Revisions from first production run
2015-06-30 Changes from user feedback and experience
2015-06-30 Last of changes before protos
2015-07-13 Enthickened lines on logos for better rendering
2015-08-27 Chg to V13, fix traces over vias
2015-09-08 Advance v# on pgs 2 and 3
2015-09-16 Changed value of DNP caps to DNP
2015-09-28 Add small series resistor on regulator bypass caps
2015-10-06 Schematic fixes from QC feedback
2015-11-11 Fix USB port anchoring to isolate shield from ground
2016-04-01 created panel v14
2018-12-10 Rename SparkFun_FreeSoC2.brd to SparkFun_FreeSoC2_V14.brd
2018-12-10 Rename SparkFun_FreeSoC2_V14.brd to SparkFun_FreeSoC2_V1.brd
2018-12-10 Rename Eagle Files
    Merge conflict. Updating names and saving before merging V14.
2018-12-10 Remove Old Eagle Files
    Remove Eagle Files to remedy merge conflict.
2018-12-10 V14 Files
    Mike Hord's Fix USB port anchoring to isolate shield from ground (from the V12 branch). There was a merge conflict so I downloaded the files manually to my computer before re-uploading.
2018-12-10 Rename SparkFun_FreeSoC2.brd to Hardware/SparkFun_FreeSoC2.brd
2018-12-10 Update path
